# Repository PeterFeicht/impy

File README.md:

Bachelor's Thesis
=================

This project contains all of the stuff from my [bachelor's thesis](thesis.pdf).

The goal is to create an impedance spectrometer based on the
*Impedance Converter Network Analyzer* chip [AD5933][1] from Analog Devices.

The device uses an [STM32F4 Discovery board][2] by ST for interfacing with a PC
and MATLAB for controlling the measurement parameters.

[1]: http://www.analog.com/en/digital-to-analog-converters/direct-digital-synthesis-dds/ad5933/products/product.html
    "Analog Devices product page"
[2]: http://www.st.com/stm32f4-discovery "ST product page"
[3]: http://www.ti.com/tool/tmdssk3358 "TI product page"

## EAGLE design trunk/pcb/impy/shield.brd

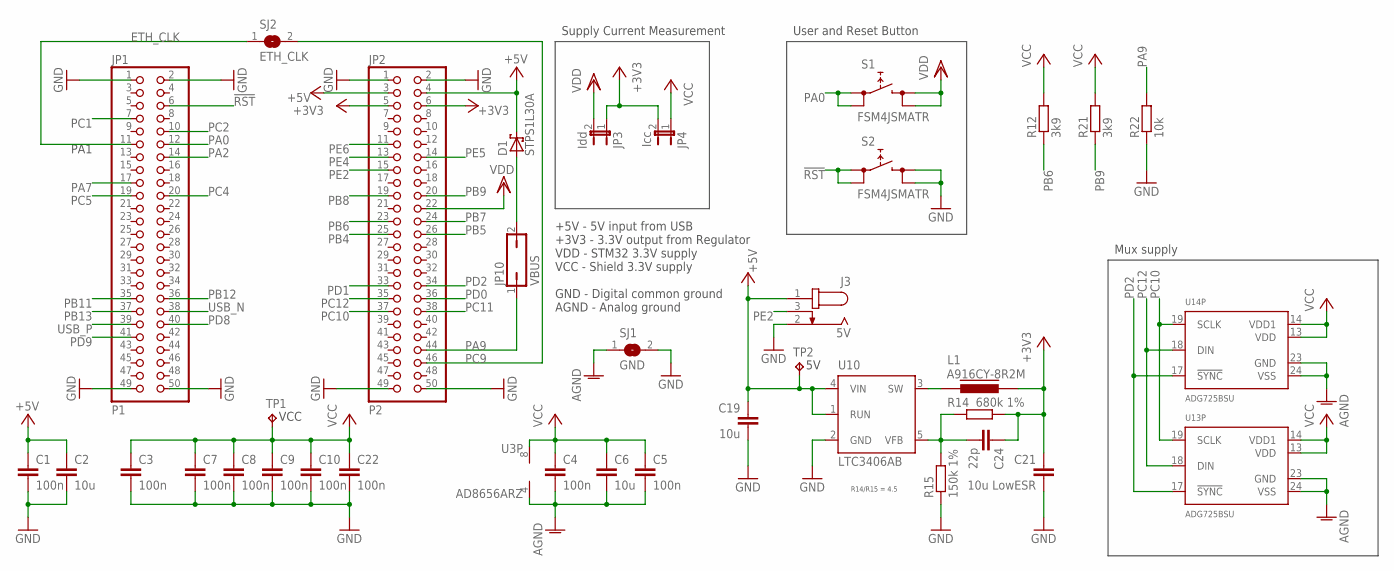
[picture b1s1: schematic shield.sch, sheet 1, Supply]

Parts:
C1, C3, C4, C5, C7, C8, C9, C10, C22: 100n; C0603
C2, C6: 10u; C0603
C19: 10u; C3216
C21: 10u LowESR; C3216
C24: 22p; C0603
D1: STPS1L30A; DO214AC
J3: 5V; JACK-SMD2.5
JP1: P1; 2X25-F
JP2: P2; 2X25-F
JP3: Idd; JP1
JP4: Icc; JP1
JP10: VBUS; JP1
L1: A916CY-8R2M; D63CB
R12, R21: 3k9; R0603
R14: 680k 1%; R0603
R15: 150k 1%; R0603
R22: 10k; R0603
S1, S2: FSM4JSMATR; FSM
SJ1: GND; SJ
SJ2: ETH_CLK; SJ
TP1, TP2: TPTP20R; TP20R
U3: AD8656ARZ; SOIC8
U10: LTC3406AB; TSOT23-5
U13, U14: ADG725BSU; TQFP48

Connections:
!RST: JP1.6, S2.1 (0), S2.2 (0)
+3V3: C21.1, C24.1, JP2.5, JP2.6, JP3.1, JP4.2, L1.2, R14.2
+5V: C1.1, C2.1, C19.1, D1.C, J3.1, JP2.3, JP2.4, TP2.TP, U10.1 (RUN), U10.4 (VIN); also elsewhere on the board
AGND: C4.2, C5.2, C6.2, SJ1.1, U3.4 (V-), U13.23 (GND), U13.24 (VSS), U14.23 (GND), U14.24 (VSS); also elsewhere on the board
ETH_CLK: JP1.11, SJ2.1; also elsewhere on the board
GND: C1.2, C2.2, C3.2, C7.2, C8.2, C9.2, C10.2, C19.2, C21.2, C22.2, J3.2 (3), JP1.1, JP1.2, JP1.49, JP1.50, JP2.1, JP2.2, JP2.49, JP2.50, R15.1, R22.1, S2.3 (1), S2.4 (1), SJ1.2, U10.2 (GND); also elsewhere on the board
unnamed: D1.A, JP10.2
unnamed: C24.2, R14.1, R15.2, U10.5 (VFB)
unnamed: L1.1, U10.3 (SW)
PA0: JP1.12, S1.1 (0), S1.2 (0)
PA2: JP1.14; also elsewhere on the board
PA7: JP1.17; also elsewhere on the board
PA9: JP2.44, JP10.1, R22.2
PB4: JP2.25; also elsewhere on the board
PB5: JP2.26; also elsewhere on the board
PB6: JP2.23, R12.1; also elsewhere on the board
PB7: JP2.24; also elsewhere on the board
PB8: JP2.19; also elsewhere on the board
PB9: JP2.20, R21.1; also elsewhere on the board
PB11: JP1.35; also elsewhere on the board
PB12: JP1.36; also elsewhere on the board
PB13: JP1.37; also elsewhere on the board
PC1: JP1.7; also elsewhere on the board
PC2: JP1.10; also elsewhere on the board
PC4: JP1.20; also elsewhere on the board
PC5: JP1.19; also elsewhere on the board
PC9: JP2.46, SJ2.2
PC10: JP2.37, U13.19 (SCLK), U14.19 (SCLK); also elsewhere on the board
PC11: JP2.38; also elsewhere on the board
PC12: JP2.35, U13.18 (DIN), U14.18 (DIN); also elsewhere on the board
PD0: JP2.36; also elsewhere on the board
PD1: JP2.33; also elsewhere on the board
PD2: JP2.34, U13.17 (!SYNC), U14.17 (!SYNC)
PD8: JP1.40; also elsewhere on the board
PD9: JP1.41; also elsewhere on the board
PE2: J3.3 (2), JP2.15
PE4: JP2.13; also elsewhere on the board
PE5: JP2.14; also elsewhere on the board
PE6: JP2.11; also elsewhere on the board
USB_N: JP1.38; also elsewhere on the board
USB_P: JP1.39; also elsewhere on the board
VCC: C3.1, C4.1, C5.1, C6.1, C7.1, C8.1, C9.1, C10.1, C22.1, JP4.1, R12.2, R21.2, TP1.TP, U3.8 (V+), U13.13 (VDD), U13.14 (VDD1), U14.13 (VDD), U14.14 (VDD1); also elsewhere on the board
VDD: JP2.22, JP3.2, S1.3 (1), S1.4 (1); also elsewhere on the board

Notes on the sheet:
+5V - 5V input from USB +3V3 - 3.3V output from Regulator VDD - STM32 3.3V supply VCC - Shield 3.3V supply GND - Digital common ground AGND - Analog ground
Supply Current Measurement
PA1
User and Reset Button
R14/R15 = 4.5
Mux supply

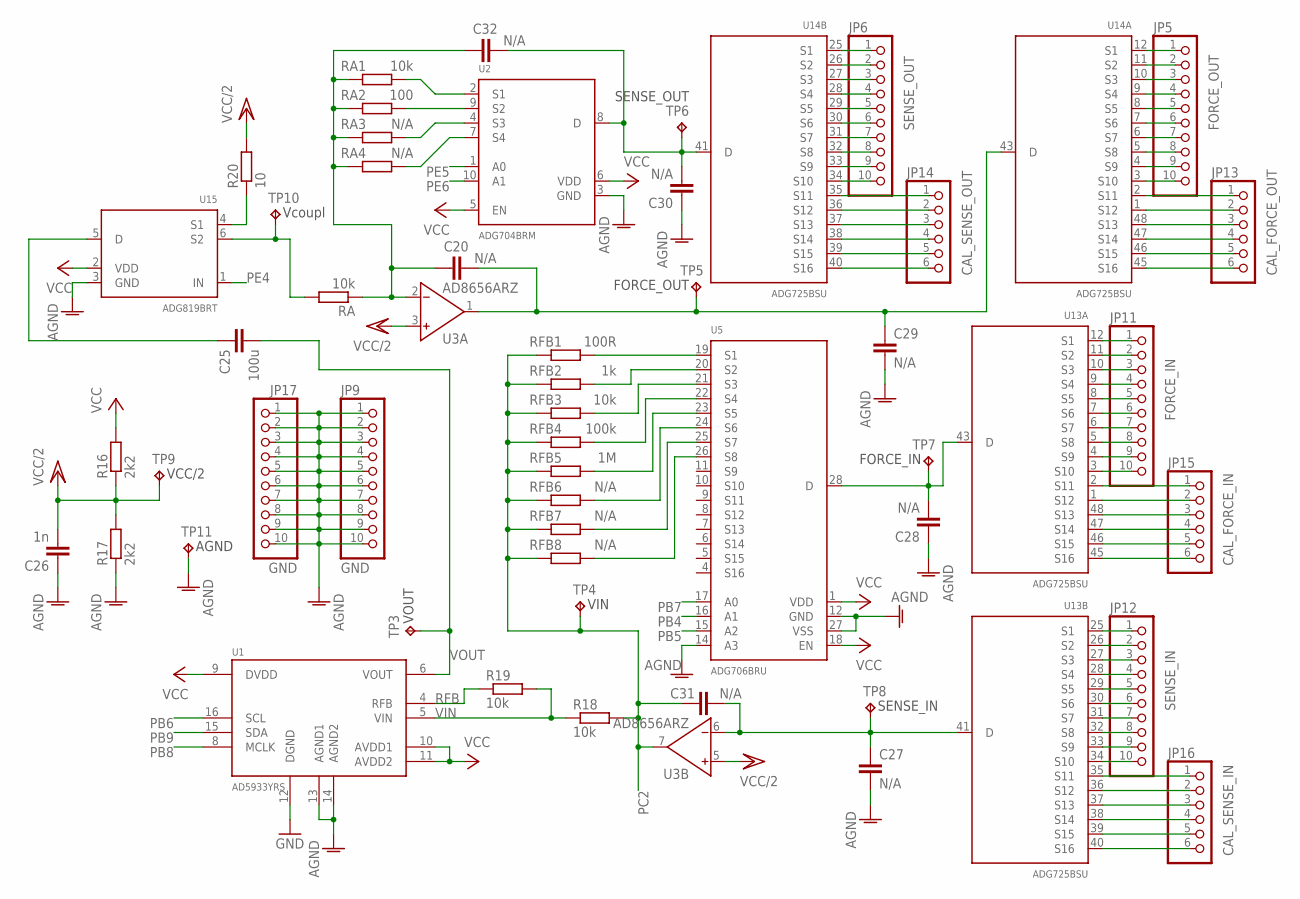
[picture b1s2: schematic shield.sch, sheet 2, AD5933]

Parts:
C20, C31, C32: N/A; C0603
C25: 100u; C1206
C26: 1n; C0603
C27, C28, C29, C30: N/A; C0805
JP5: FORCE_OUT; 1X10
JP6: SENSE_OUT; 1X10
JP9, JP17: GND; 1X10
JP11: FORCE_IN; 1X10
JP12: SENSE_IN; 1X10
JP13: CAL_FORCE_OUT; 1X06
JP14: CAL_SENSE_OUT; 1X06
JP15: CAL_FORCE_IN; 1X06
JP16: CAL_SENSE_IN; 1X06
R16, R17: 2k2; R0603
R18, R19: 10k; R0603
R20: 10; R0603
RA, RA1: 10k; R0603
RA2: 100; R0603
RA3, RA4: N/A; R0603
RFB1: 100R; R0603
RFB2: 1k; R0603
RFB3: 10k; R0603
RFB4: 100k; R0603
RFB5: 1M; R0603
RFB6, RFB7, RFB8: N/A; R0603
TP3, TP4, TP5, TP6, TP7, TP8, TP9, TP10: TPTP20R; TP20R
TP11: TPPAD1-13; P1-13
U1: AD5933YRS; SSOP16
U2: ADG704BRM; MSOP10
U3: AD8656ARZ; SOIC8
U5: ADG706BRU; TSSOP28
U13, U14: ADG725BSU; TQFP48
U15: ADG819BRT; SOT23-6

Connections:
AGND: C26.1, C27.2, C28.1, C29.2, C30.1, JP9.1, JP9.2, JP9.3, JP9.4, JP9.5, JP9.6, JP9.7, JP9.8, JP9.9, JP9.10, JP17.1, JP17.2, JP17.3, JP17.4, JP17.5, JP17.6, JP17.7, JP17.8, JP17.9, JP17.10, R17.1, TP11.TP, U1.13 (AGND1), U1.14 (AGND2), U2.3 (GND), U5.12 (GND), U5.14 (A3), U5.27 (VSS), U15.3 (GND); also elsewhere on the board
GND: U1.12 (DGND); also elsewhere on the board
unnamed 6: C31.1, R18.2, RFB1.2, RFB2.2, RFB3.2, RFB4.2, RFB5.2, RFB6.2, RFB7.2, RFB8.2, TP4.TP, U3.7 (OUT); also elsewhere on the board
unnamed: RA.2, TP10.TP, U15.6 (S2)
unnamed: C20.1, C32.1, RA.1, RA1.1, RA2.1, RA3.1, RA4.1, U3.2 (IN-)
unnamed: RA3.2, U2.4 (S3)
unnamed: RA4.2, U2.7 (S4)
unnamed: RFB1.1, U5.19 (S1)
unnamed: RFB2.1, U5.20 (S2)
unnamed: RFB3.1, U5.21 (S3)
unnamed: RFB4.1, U5.22 (S4)
unnamed: RFB5.1, U5.23 (S5)
unnamed: RFB6.1, U5.24 (S6)
unnamed: C27.1, C31.2, TP8.TP, U3.6 (IN-), U13.41 (D)
unnamed: C28.2, TP7.TP, U5.28 (D), U13.43 (D)
unnamed: C20.2, C29.1, TP5.TP, U3.1 (OUT), U14.43 (D)
unnamed: C30.2, C32.2, TP6.TP, U2.8 (D), U14.41 (D)
unnamed: JP12.1, U13.25 (S1)
unnamed: JP12.2, U13.26 (S2)
unnamed: JP12.3, U13.27 (S3)
unnamed: JP12.4, U13.28 (S4)
unnamed: JP12.5, U13.29 (S5)
unnamed: JP12.6, U13.30 (S6)
unnamed: JP12.7, U13.31 (S7)
unnamed: JP12.8, U13.32 (S8)
unnamed: JP12.9, U13.33 (S9)
unnamed: JP12.10, U13.34 (S10)
unnamed: JP11.1, U13.12 (S1)
unnamed: JP11.2, U13.11 (S2)
unnamed: JP11.3, U13.10 (S3)
unnamed: JP11.4, U13.9 (S4)
unnamed: JP11.5, U13.8 (S5)
unnamed: JP11.6, U13.7 (S6)
unnamed: JP11.7, U13.6 (S7)
unnamed: JP11.8, U13.5 (S8)
unnamed: JP11.9, U13.4 (S9)
unnamed: JP11.10, U13.3 (S10)
unnamed: JP5.1, U14.12 (S1)
unnamed: JP5.2, U14.11 (S2)
unnamed: JP5.3, U14.10 (S3)
unnamed: JP5.4, U14.9 (S4)
unnamed: JP5.5, U14.8 (S5)
unnamed: JP5.6, U14.7 (S6)
unnamed: JP5.7, U14.6 (S7)
unnamed: JP5.8, U14.5 (S8)
unnamed: JP5.9, U14.4 (S9)
unnamed: JP5.10, U14.3 (S10)
unnamed: JP6.1, U14.25 (S1)
unnamed: JP6.2, U14.26 (S2)
unnamed: JP6.3, U14.27 (S3)
unnamed: JP6.4, U14.28 (S4)
unnamed: JP6.5, U14.29 (S5)
unnamed: JP6.6, U14.30 (S6)
unnamed: JP6.7, U14.31 (S7)
unnamed: JP6.8, U14.32 (S8)
unnamed: JP6.9, U14.33 (S9)
unnamed: JP6.10, U14.34 (S10)
unnamed: JP13.1, U14.2 (S11)
unnamed: JP13.2, U14.1 (S12)
unnamed: JP13.3, U14.48 (S13)
unnamed: JP13.4, U14.47 (S14)
unnamed: JP13.5, U14.46 (S15)
unnamed: JP13.6, U14.45 (S16)
unnamed: JP14.1, U14.35 (S11)
unnamed: JP14.2, U14.36 (S12)
unnamed: JP14.3, U14.37 (S13)
unnamed: JP14.4, U14.38 (S14)
unnamed: JP14.5, U14.39 (S15)
unnamed: JP14.6, U14.40 (S16)
unnamed: JP15.1, U13.2 (S11)
unnamed: JP15.2, U13.1 (S12)
unnamed: JP15.3, U13.48 (S13)
unnamed: JP15.4, U13.47 (S14)
unnamed: JP15.5, U13.46 (S15)
unnamed: JP15.6, U13.45 (S16)
unnamed: JP16.1, U13.35 (S11)
unnamed: JP16.2, U13.36 (S12)
unnamed: JP16.3, U13.37 (S13)
unnamed: JP16.4, U13.38 (S14)
unnamed: JP16.5, U13.39 (S15)
unnamed: JP16.6, U13.40 (S16)
unnamed: RA2.2, U2.9 (S2)
unnamed: RA1.2, U2.2 (S1)
unnamed: RFB7.1, U5.25 (S7)
unnamed: RFB8.1, U5.26 (S8)
unnamed: C25.1, U15.5 (D)
unnamed: R20.1, U15.4 (S1)
PB4: U5.16 (A1); also elsewhere on the board
PB5: U5.15 (A2); also elsewhere on the board
PB6: U1.16 (SCL); also elsewhere on the board
PB7: U5.17 (A0); also elsewhere on the board
PB8: U1.8 (MCLK); also elsewhere on the board
PB9: U1.15 (SDA); also elsewhere on the board
PE4: U15.1 (IN); also elsewhere on the board
PE5: U2.1 (A0); also elsewhere on the board
PE6: U2.10 (A1); also elsewhere on the board
RFB: R19.1, U1.4 (RFB)
VCC: R16.2, U1.9 (DVDD), U1.10 (AVDD1), U1.11 (AVDD2), U2.5 (EN), U2.6 (VDD), U5.1 (VDD), U5.18 (EN), U15.2 (VDD); also elsewhere on the board
VCC/2: C26.2, R16.1, R17.2, R20.2, TP9.TP, U3.3 (IN+), U3.5 (IN+)
VIN: R18.1, R19.2, U1.5 (VIN)
VOUT: C25.2, TP3.TP, U1.6 (VOUT)

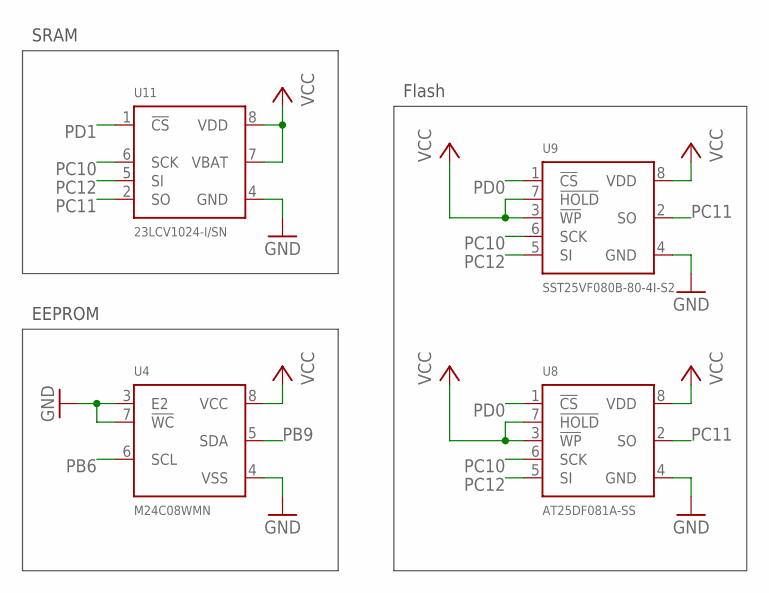
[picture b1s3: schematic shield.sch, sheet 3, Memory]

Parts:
U4: M24C08WMN; SO8
U8: AT25DF081A-SS; SO8
U9: SST25VF080B-80-4I-S2; SOIC8
U11: 23LCV1024-I/SN; SO8

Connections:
GND: U4.3 (E2), U4.4 (VSS), U4.7 (!WC), U8.4 (GND), U9.4 (GND), U11.4 (GND); also elsewhere on the board
PB6: U4.6 (SCL); also elsewhere on the board
PB9: U4.5 (SDA); also elsewhere on the board
PC10: U8.6 (SCK), U9.6 (SCK), U11.6 (SCK); also elsewhere on the board
PC11: U8.2 (SO), U9.2 (SO), U11.2 (SO); also elsewhere on the board
PC12: U8.5 (SI), U9.5 (SI), U11.5 (SI); also elsewhere on the board
PD0: U8.1 (!CS), U9.1 (!CS); also elsewhere on the board
PD1: U11.1 (!CS); also elsewhere on the board
VCC: U4.8 (VCC), U8.3 (!WP), U8.7 (!HOLD), U8.8 (VDD), U9.3 (!WP), U9.7 (!HOLD), U9.8 (VDD), U11.7 (VBAT), U11.8 (VDD); also elsewhere on the board

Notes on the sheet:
EEPROM
Flash
SRAM

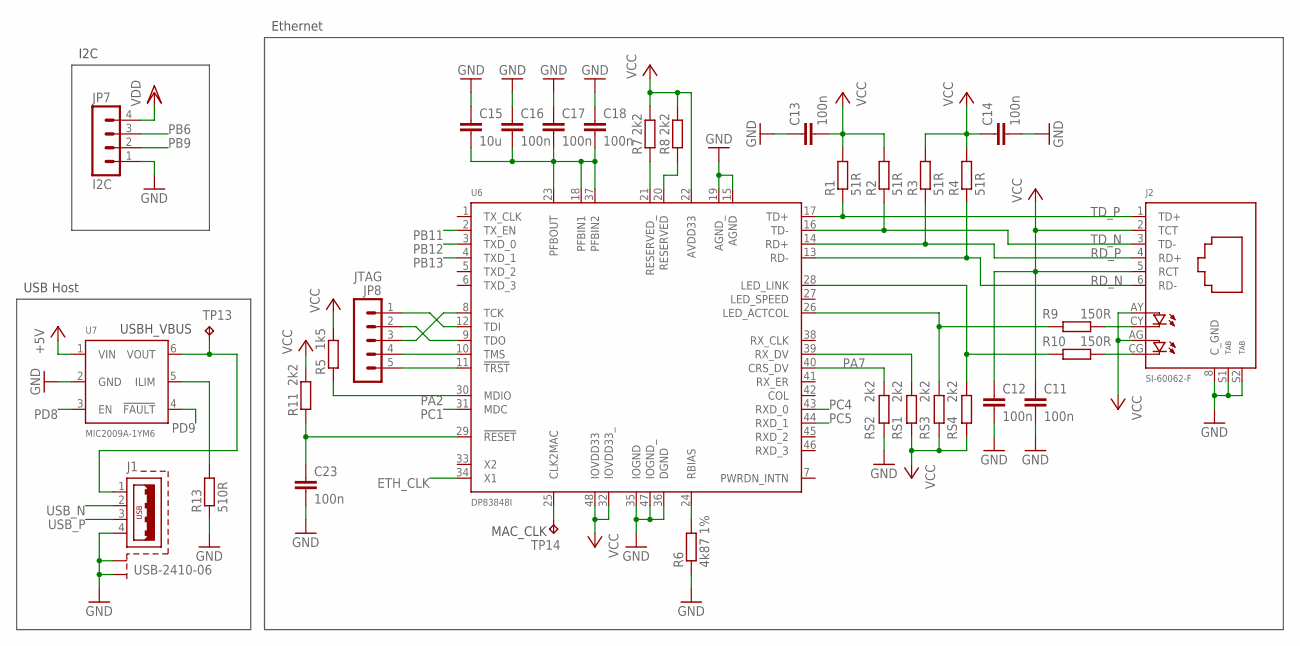
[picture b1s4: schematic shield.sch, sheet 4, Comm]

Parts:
C11, C12, C13, C14, C16, C17, C18, C23: 100n; C0603
C15: 10u; C0603
J1: USB-2410-06
J2: SI-60062-F
JP7: I2C; MA04-1
JP8: JTAG; MA05-1
R1, R2, R3, R4: 51R; R0603
R5: 1k5; R0603
R6: 4k87 1%; R0603
R7, R8, R11: 2k2; R0603
R9, R10: 150R; R0603
R13: 510R; R0603
RS1, RS2, RS3, RS4: 2k2; R0603
TP13, TP14: TPTP20R; TP20R
U6: DP83848I; LQFP48
U7: MIC2009A-1YM6; SOT23-6

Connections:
+5V: U7.1 (VIN); also elsewhere on the board
ETH_CLK: U6.34 (X1); also elsewhere on the board
GND: C11.2, C12.2, C13.1, C14.2, C15.1, C16.1, C17.1, C18.1, C23.2, J1.4 (GND), J1.S1, J1.S2, J2.8 (C_GND), J2.S1 (TAB1), J2.S2 (TAB2), JP7.1, R6.1, R13.1, RS2.2, U6.15 (AGND), U6.19 (AGND_), U6.35 (IOGND), U6.36 (DGND), U6.47 (IOGND_), U7.2 (GND); also elsewhere on the board
unnamed: J2.CY, R9.2
unnamed: RS1.2, U6.39 (RX_DV)
unnamed: R9.1, RS3.2, U6.26 (LED_ACTCOL)
unnamed: R10.1, RS4.2, U6.28 (LED_LINK)
unnamed: C15.2, C16.2, C17.2, C18.2, U6.18 (PFBIN1), U6.23 (PFBOUT), U6.37 (PFBIN2)
unnamed: J2.CG, R10.2
unnamed: J1.1 (VCC), TP13.TP, U7.6 (VOUT)
unnamed: JP8.1, U6.12 (TDI)
unnamed: JP8.2, U6.9 (TDO)
unnamed: JP8.3, U6.8 (TCK)
unnamed: JP8.4, U6.10 (TMS)
unnamed: JP8.5, U6.11 (!TRST)
unnamed: C23.1, R11.1, U6.29 (!RESET)
unnamed: R6.2, U6.24 (RBIAS)
unnamed: R8.1, U6.20 (RESERVED)
unnamed: R7.1, U6.21 (RESERVED_)
unnamed: R13.2, U7.5 (ILIM)
unnamed: TP14.TP, U6.25 (CLK2MAC)
PA2: R5.1, U6.30 (MDIO); also elsewhere on the board
PA7: RS2.1, U6.40 (CRS_DV); also elsewhere on the board
PB6: JP7.3; also elsewhere on the board
PB9: JP7.2; also elsewhere on the board
PB11: U6.2 (TX_EN); also elsewhere on the board
PB12: U6.3 (TXD_0); also elsewhere on the board
PB13: U6.4 (TXD_1); also elsewhere on the board
PC1: U6.31 (MDC); also elsewhere on the board
PC4: U6.43 (RXD_0); also elsewhere on the board
PC5: U6.44 (RXD_1); also elsewhere on the board
PD8: U7.3 (EN); also elsewhere on the board
PD9: U7.4 (!FAULT); also elsewhere on the board
RD_N: J2.6 (RD-), R4.1, U6.13 (RD-)
RD_P: J2.4 (RD+), R3.1, U6.14 (RD+)
TD_N: J2.3 (TD-), R2.1, U6.16 (TD-)
TD_P: J2.1 (TD+), R1.1, U6.17 (TD+)
USB_N: J1.2 (D-); also elsewhere on the board
USB_P: J1.3 (D+); also elsewhere on the board
VCC: C11.1, C12.1, C13.2, C14.1, J2.2 (TCT), J2.5 (RCT), J2.AG, J2.AY, R1.2, R2.2, R3.2, R4.2, R5.2, R7.2, R8.2, R11.2, RS1.1, RS3.1, RS4.1, U6.22 (AVDD33), U6.32 (IOVDD33_), U6.48 (IOVDD33); also elsewhere on the board
VDD: JP7.4; also elsewhere on the board

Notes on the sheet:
I2C
Ethernet
USB Host

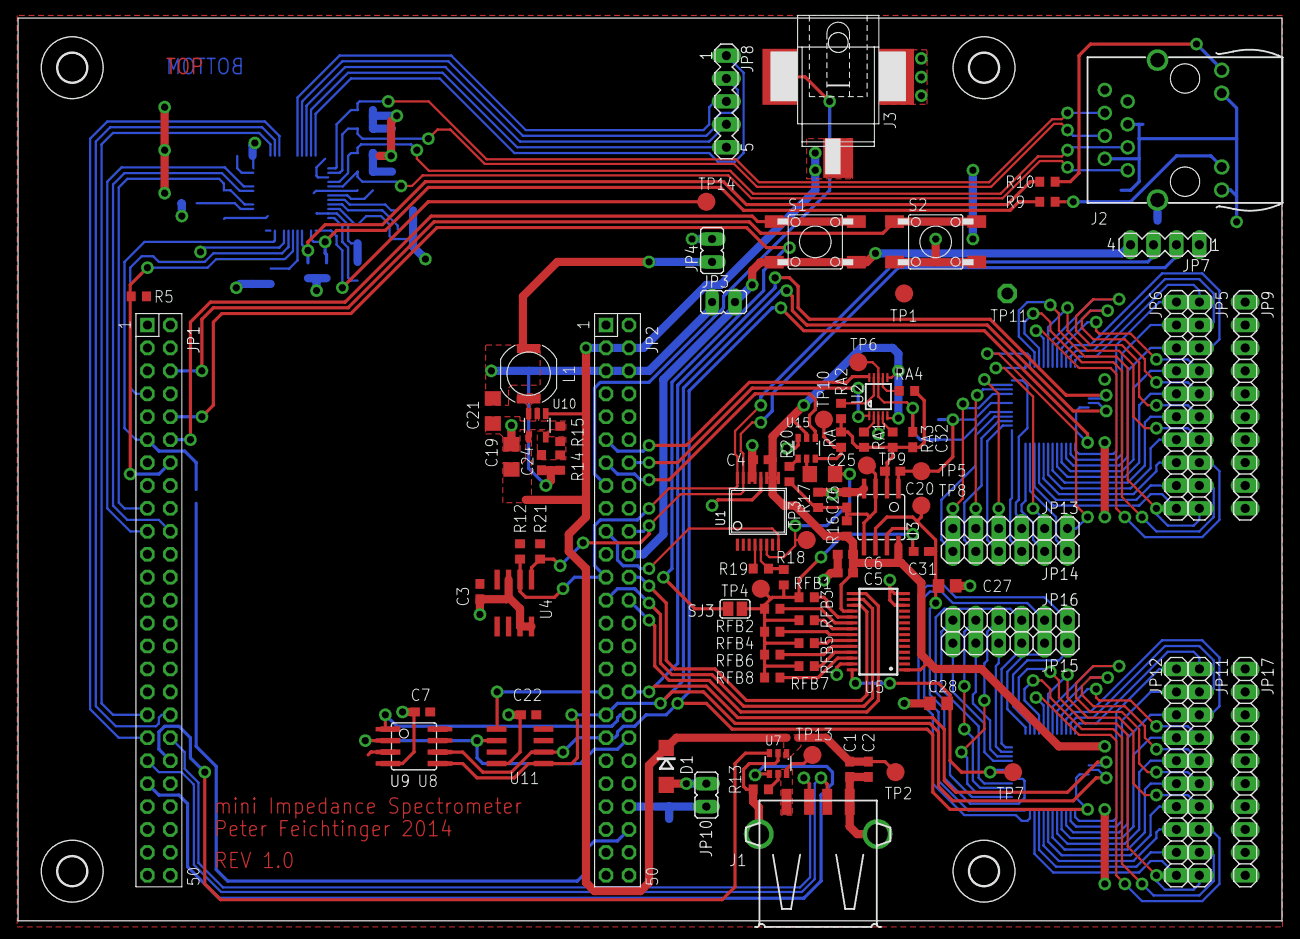
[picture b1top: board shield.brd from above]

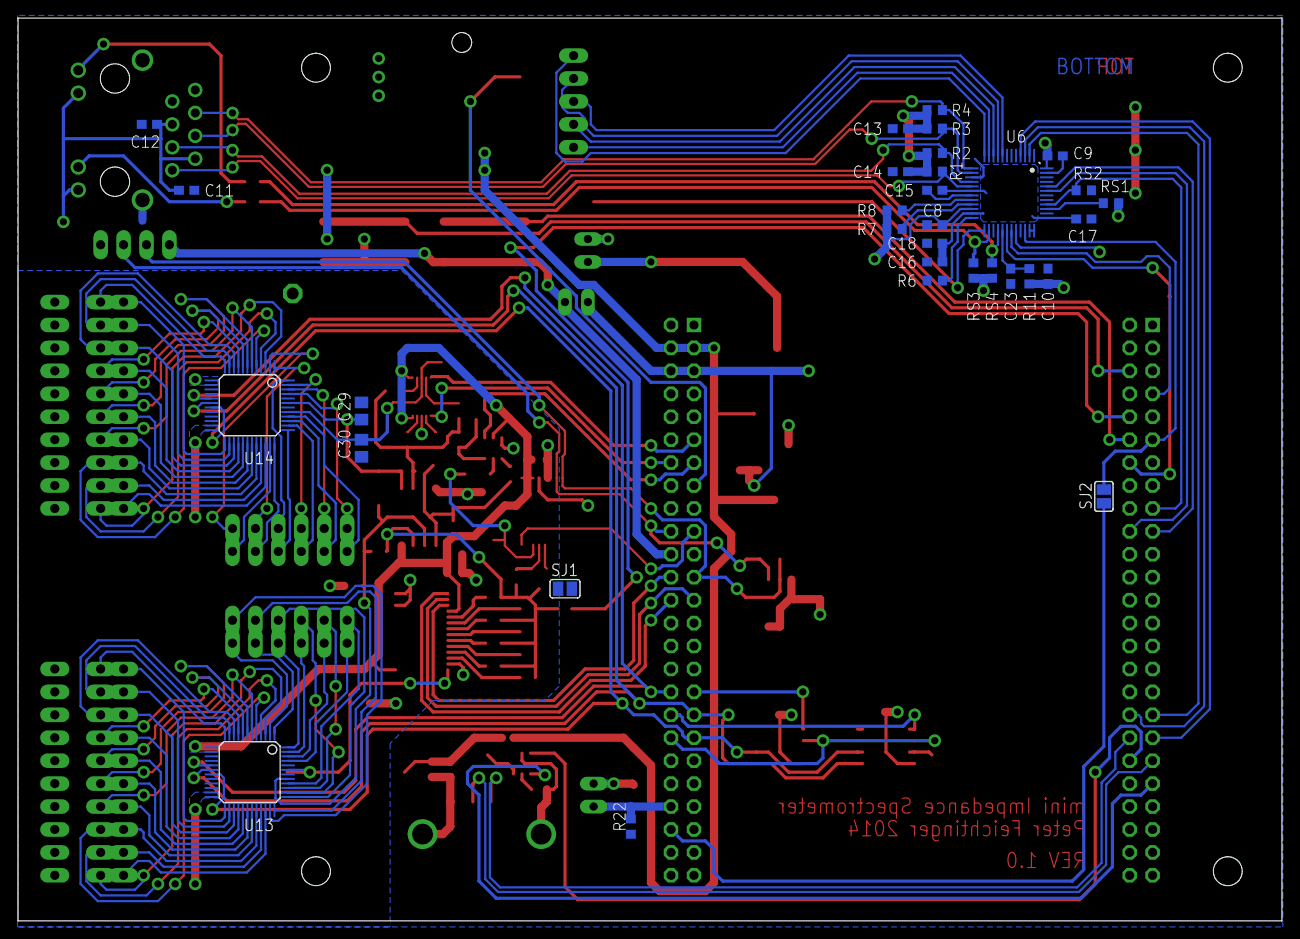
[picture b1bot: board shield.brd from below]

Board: 2 copper layers, 140.0 x 100.0 mm, 129 parts (32 on the bottom side), 154 nets.

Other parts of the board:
SJ3: OVFL; SJ
U$1, U$2, U$3, U$4: 3,2

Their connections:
unnamed 6: SJ3.2; also elsewhere on the board
PC2: SJ3.1; also elsewhere on the board

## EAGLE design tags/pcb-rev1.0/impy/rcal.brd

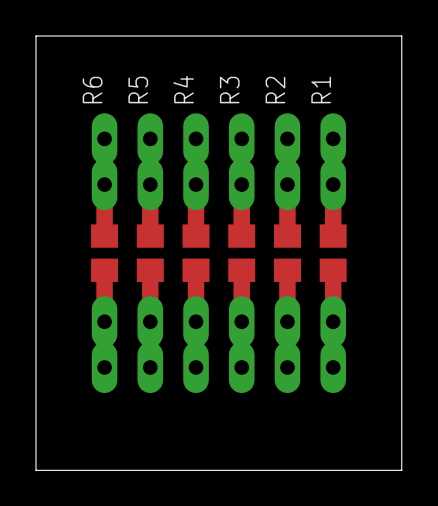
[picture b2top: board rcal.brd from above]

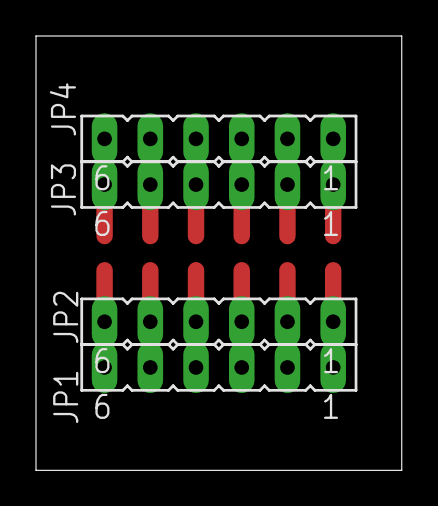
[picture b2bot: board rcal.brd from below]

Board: 2 copper layers, 20.3 x 24.1 mm, 10 parts (4 on the bottom side), 12 nets.

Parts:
JP1, JP2, JP3, JP4: FE06
R1: 10R; R0805
R2: 100R; R0805
R3: 1k; R0805
R4: 10k; R0805
R5: 100k; R0805
R6: 1M; R0805

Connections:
unnamed: JP1.6, JP2.6, R1.1
unnamed: JP1.5, JP2.5, R2.1
unnamed: JP1.4, JP2.4, R3.1
unnamed: JP1.3, JP2.3, R4.1
unnamed: JP1.2, JP2.2, R5.1
unnamed: JP1.1, JP2.1, R6.1
unnamed: JP3.6, JP4.6, R1.2
unnamed: JP3.5, JP4.5, R2.2
unnamed: JP3.4, JP4.4, R3.2
unnamed: JP3.3, JP4.3, R4.2
unnamed: JP3.2, JP4.2, R5.2
unnamed: JP3.1, JP4.1, R6.2

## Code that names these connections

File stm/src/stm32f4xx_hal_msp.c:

/**
 * @file    stm32f4xx_hal_msp.c
 * @author  Peter Feichtinger
 * @date    14.04.2014
 * @brief   Provides MSP initialization code.
 */

// Includes -------------------------------------------------------------------
#include "stm32f4xx_hal.h"

// Exported functions ---------------------------------------------------------

/**
 * Initializes the I2C MSP.
 * 
 * @param hi2c I2C handle
 */
void HAL_I2C_MspInit(I2C_HandleTypeDef* hi2c) {
    GPIO_InitTypeDef GPIO_InitStruct;
    if(hi2c->Instance == I2C1) {
        __I2C1_CLK_ENABLE();
        
        /*
         * GPIO configuration:
         *  PB6: I2C1_SCL
         *  PB9: I2C1_SDA
         */
        GPIO_InitStruct.Pin = GPIO_PIN_6 | GPIO_PIN_9;
        GPIO_InitStruct.Mode = GPIO_MODE_AF_OD;
        GPIO_InitStruct.Pull = GPIO_NOPULL;
        GPIO_InitStruct.Speed = GPIO_SPEED_LOW;
        GPIO_InitStruct.Alternate = GPIO_AF4_I2C1;
        HAL_GPIO_Init(GPIOB, &GPIO_InitStruct);
        
        // Set I2C interrupt to the lowest priority
        HAL_NVIC_SetPriority(I2C1_EV_IRQn, 10, 0);
        NVIC_EnableIRQ(I2C1_EV_IRQn);
    }
}

/**
 * De-initializes the I2C MSP.
 * 
 * @param hi2c I2C handle
 */
void HAL_I2C_MspDeInit(I2C_HandleTypeDef* hi2c) {
    if(hi2c->Instance == I2C1) {
        __I2C1_CLK_DISABLE();
        HAL_GPIO_DeInit(GPIOB, GPIO_PIN_6 | GPIO_PIN_9);
        NVIC_DisableIRQ(I2C1_EV_IRQn);
    }
}

/**
 * Initializes the SPI MSP.
 * 
 * @param hspi SPI handle
 */
void HAL_SPI_MspInit(SPI_HandleTypeDef* hspi) {
    GPIO_InitTypeDef GPIO_InitStruct;
    if(hspi->Instance == SPI3) {
        __SPI3_CLK_ENABLE();
        
        /*
         * GPIO configuration:
         *  PC10: SPI3_SCK
         *  PC11: SPI3_MISO
         *  PC12: SPI3_MOSI
         */
        GPIO_InitStruct.Pin = GPIO_PIN_10 | GPIO_PIN_11 | GPIO_PIN_12;
        GPIO_InitStruct.Mode = GPIO_MODE_AF_PP;
        GPIO_InitStruct.Pull = GPIO_NOPULL;
        GPIO_InitStruct.Speed = GPIO_SPEED_HIGH;
        GPIO_InitStruct.Alternate = GPIO_AF6_SPI3;
        HAL_GPIO_Init(GPIOC, &GPIO_InitStruct);
        
        // Set SPI interrupt to the lowest priority
        HAL_NVIC_SetPriority(SPI3_IRQn, 10, 0);
        NVIC_EnableIRQ(SPI3_IRQn);
    }
}

/**
 * De-initializes the SPI MSP.
 * 
 * @param hspi SPI handle
 */
void HAL_SPI_MspDeInit(SPI_HandleTypeDef* hspi) {
    if(hspi->Instance == SPI3) {
        __SPI3_CLK_DISABLE();
        HAL_GPIO_DeInit(GPIOD, GPIO_PIN_0 | GPIO_PIN_1 | GPIO_PIN_2);
        HAL_GPIO_DeInit(GPIOC, GPIO_PIN_10 | GPIO_PIN_11 | GPIO_PIN_12);
        NVIC_DisableIRQ(SPI3_IRQn);
    }
}

/**
 * Initializes the TIM MSP.
 * 
 * @param htim TIM handle
 */
void HAL_TIM_Base_MspInit(TIM_HandleTypeDef* htim) {
    GPIO_InitTypeDef GPIO_InitStruct;
    if(htim->Instance == TIM3) {
        __TIM3_CLK_ENABLE();
        HAL_NVIC_SetPriority(TIM3_IRQn, 7, 0);
        NVIC_EnableIRQ(TIM3_IRQn);
        
    } else if(htim->Instance == TIM10) {
        __TIM10_CLK_ENABLE();
        
        /*
         * GPIO configuration:
         *  PB8: TIM10_CH1
         */
        GPIO_InitStruct.Pin = GPIO_PIN_8;
        GPIO_InitStruct.Mode = GPIO_MODE_AF_PP;
        GPIO_InitStruct.Pull = GPIO_NOPULL;
        GPIO_InitStruct.Speed = GPIO_SPEED_FAST;
        GPIO_InitStruct.Alternate = GPIO_AF3_TIM10;
        HAL_GPIO_Init(GPIOB, &GPIO_InitStruct);
    }
}

/**
 * De-initializes the TIM MSP.
 * 
 * @param htim TIM handle
 */
void HAL_TIM_Base_MspDeInit(TIM_HandleTypeDef* htim) {
    if(htim->Instance == TIM3) {
        __TIM3_CLK_DISABLE();
        NVIC_DisableIRQ(TIM3_IRQn);
        
    } else if(htim->Instance == TIM10) {
        __TIM10_CLK_DISABLE();
        HAL_GPIO_DeInit(GPIOB, GPIO_PIN_8);
    }
}

// ----------------------------------------------------------------------------

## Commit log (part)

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2014-06-24 * stm/impy: (main.c) Change default values for start frequency, feedback resistor and autorange. (command-line.txt) Update documentation for changed values.
2014-06-24 * stm/impy: (ad5933.h) Add constant for lowest sweep frequencies with the respective clock sources. Change order of constant declarations to be sorted from high to low.
2014-06-24 * stm/impy: (ad5933.h) Remove constant for timer handle and add argument to AD5933_Init function instead. (ad5933.c) Add timer handle variable and argument to AD5933_Init function. (main.c) Add timer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
2014-06-24 * stm/impy: (ad5933.c) Implement clock source change during a sweep.
    The phase error when using a different clock source than was calibrated with is considerable, maybe we need to do a phase calibration in each frequency range. Therefore the gain factor structures wou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
    The alternative would be to let the user manage multiple gain factors for different frequency ranges.
2014-06-27 * stm/impy: (stm32f4xx_it.c) Change hard fault handler to flash the red LED.
2014-06-28 * stm/impy: (main.c) Update Board_Calibrate to new AD5933 driver calibration interface. (convert.c) Update Convert_ConvertGainFactor to handle new gain factor format.
2014-06-29 * stm/impy: (usbd_vcp_if.c) Don't call console with empty command.
2014-06-29 * stm/impy: (ad5933.c) Remove unnecessary private function AD5933_NeedClockChange, only one line that's used in one place.
2014-06-29 * matlab: Add script to test impy_getall function.
2014-06-29 * matlab: (readdata.m, readdata_p.m) Add proper documentation to functions.
2014-06-29 * matlab: Add script to test the whole measurement process, including functions impy_setsweep, impy_calibrate, impy_start, impy_poll and impy_read (both polar and raw format), with option to compare 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
2014-06-30 * matlab: (impy_setsweep.m) Add documentation for required and optional fields.
2014-06-30 * stm/impy: (console.c) Remove debug commands char-from-flag, read and ad-i2c because they are no longer needed.
2014-06-30 * stm/impy: (console.h, console.c) Change signature of Console_ProcessLine to take a Console_Interface pointer. (console.c) Add variable for the interface.
2014-06-30 * stm/impy: (console.c) Replace all calls to VCP functions with calls to interface pointers. As a side note, this adds 840 bytes to the code size.
2014-06-30 * stm/impy: (ad5933.c, console.c, convert.c, main.c, usbd_vcp_if.c) Replace some parameter checks by assert or assert_param macro.
2014-07-04 * stm/impy: (ad5933.c) Improve documentation and add some structure comments.
2014-07-05 * stm/impy: Update STM32CubeF4 HAL and USB drivers to version 1.3.0.
2014-07-05 * stm/impy: (eeprom.h, eeprom.c) Rename functions with shorter module prefix.
2014-07-05 * stm/impy: (console.c) Add debug command output to output a single frequency on a specified port.
2014-07-05 * pcb/impy: (ime.dru) Change distance copper/dimension to 80mil.
2014-07-05 * stm/impy: (eeprom.h) Add structure definitions for configuration and settings buffers, add constants for memory organization and change access methods to read and write the new structures instead o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
2014-07-05 * stm/impy: (eeprom.h) Add macro to build I2C device address. Improve documentation. Add constant for EEPROM size.
2014-07-05 * stm/impy: Add CRC HAL driver file to build. (stm32f4xx_hal_conf.h) Enable HAL CRC module. (main.h, main.c) Add CRC handle variable. (mx_init.c) Add CRC initialization.
2014-07-05 * stm/impy: (eeprom.h) Change EE_TimerCallback to return current driver status.
2014-07-06 * stm/impy: (eeprom.h) Add status definitions for different writes.
2014-07-06 * stm/impy: (eeprom.h) Add constant for the EEPROM page size.
2014-07-06 * stm/impy: (eeprom.c) Fix bad buffer size in CRC calculation.
2014-07-06 * stm/impy: (eeprom.c) Add status assertion to exported functions.
2014-07-06 * stm/impy/system: (usbd_def.h) Avoid warning by conditionally defining HIBYTE and LOBYTE macros.
2014-07-06 * stm/impy: (eeprom.h) Avoid warning by conditionally defining HIBYTE and LOBYTE macros.
2014-07-06 * stm/impy: (mx_init.h, mx_init.c) Add function MX_Init_Ethernet to initialize Ethernet specific things, at the moment only the PLLI2S and MCO2 are configured. (mx_init.c) Remove conditional GPIO ana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
2014-07-06 * stm/impy: (console.c) Add parameter checks and unused attributes to some Ethernet and USB processing functions.
2014-07-06 * stm/impy: (main.h, main.c, console.c) Remove constant PORT_MIN, the first port is always 0.
2014-07-06 * stm/impy: (eeprom.h) Add fields for external memory sizes to EEPROM_ConfigurationBuffer. (main.c) Add default values to configuration structure initialization.
2014-07-06 * stm/impy: (eeprom.h, eeprom.c) Add driver prefix to function EE_GetStatus.
2014-07-06 * stm/impy: (main.h) Add constant for the state of the EEPROM E2 pin.
2014-07-06 * stm/impy: (eeprom.c) Fix data type for 16 bit addition.
2014-07-06 * stm/impy: (ad5933.h, mx_init.c) Update documentation.
2014-07-06 * stm/impy: (eeprom.h, eeprom.c) Make EE_IsBusy public.
2014-07-06 * stm/impy: (main.h) Add constant for EEPROM write interval and prototype for MarkSettingsDirty. (main.c) Implement writing settings to EEPROM, works beautifully.
2014-07-06 * stm/impy: (main.h, main.c) Add function WriteConfiguration to initiate a configuration write. (main.c) Add Ethernet initialization (just the call).
2014-07-07 * stm/impy: (mx_init.c) Fix missing CRC peripheral clock enable.
2014-07-07 * stm/impy: (ad5933.h) Change NUMEL macro.
2014-07-07 * stm/impy: (console.h) Add Console_CalibrateCallback function. (console.c) Add missing documentation. Change 'board calibrate' command to use callback instead of waiting. (main.c) Change calibration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
2014-07-09 * latex/presentations: Add second presentation with pictures. Add pr2.pdf to ignore list.
2014-07-10 * stm/impy: (console.c) Add debug command dump to dump EEPROM contents to console.
2014-07-11 * stm/impy: (util.h, util.c) Add functions MacAddressFromString and StringFromMacAddress to convert MAC addresses. (util.c) Add private function Util_ConvertHexDigit.
2014-07-11 * stm/impy: (console.c) Implement setup command. (string_en.h) Add strings for setup command.
2014-07-11 * stm/impy: (console.c) Add Ethernet, SRAM and flash memory info to 'board info' command.
2014-07-11 * stm/impy: (command-line.txt) Add possible MAC address format to setup help topic.
2014-07-11 * stm/impy: (main.c) Replace GCC pragmas with attributes for main function.
2014-07-11 * stm/impy: (util.c) Add parameter checks to MacAddressFromString and StringFromMacAddress.
2014-07-11 * stm/impy: (usbd_vcp_if.c) Remove unnecessary TODO tag.
2014-07-11 * stm/impy: (eeprom.c) Change EE_Init to check for EEPROM response and return success or error depending on the result, useful for dynamically determining if an EEPROM is fitted.
2014-07-11 * stm/impy: (main.h) Remove constant for EEPROM population and add extern variable declaration board_has_eeprom. (console.c) Use variable board_has_eeprom instead of constant.
2014-07-11 * stm/impy: (main.c) Replace duplicate code by call to MarkSettingsDirty in InitFromEEPROM.
2014-07-11 * stm/impy: (command-line.txt) Fix typo.
2014-07-11 * stm/impy: Add binary and documentation directories to ignore list. Add Doxyfile.
2014-07-11 * stm/impy: (usbd_vcp.c) Fix incomplete transfer when the size is a multiple of the packet size. This resolves issue 31.
2014-07-12 * stm/impy: (console.c) Remove debug command tim.
2014-07-12 * stm/impy: (ad5933.h, main.c) Minor comment changes.
2014-07-14 * stm/impy: (command-line.txt) Change range selection procedure, the highest current should be no more than 10mA to guarantee 3V output voltage swing. Add 'usb delete' command.
2014-07-15 * pcb/impy: (shield.sch) Add various compensation capacitors to the op amps.
2014-07-15 * pcb/impy: (shield.sch, shield.brd) Add solder jumper for overflow detect signal.
2014-07-15 * pcb/impy: (eagle.epf) Update EAGLE preference file.
2014-07-16 * latex/thesis: (dank.tex) Write acknowledgment, maybe I'll add some more people to thank.
2014-10-22 * latex/thesis: (thesis.tex) Change the document structure.
2014-10-22 * latex/thesis: (header.tex) Add file defs.tex for custom command definitions and move stuff from header.tex there.
2014-10-22 * latex/thesis: (thesis.tex) Include defs file.
2014-10-22 * stm/impy: Format the source code with a new style, opening braces are mostly on the same line now.
2014-10-22 * latex/thesis: (software.tex) Write Software chapter, mostly finished.
2014-10-24 * latex/thesis: (api.tex) Write API chapter, mostly finished.
2014-10-24 * stm/impy: (command-line.txt) Improve usage text.
2014-12-02 * latex/thesis: (software.tex, api.tex) Change wording and a section title.
2014-12-02 * latex/thesis: (hardware.tex) Start hardware chapter (introduction finished, analog front end started). * Add images: STM32F4 Discovery board, AD5933 block diagram and AFE block diagram.
2014-12-03 * latex/thesis: (hardware.tex) Add subsection for the AD5933 measurement procedure.
2014-12-03 * latex/thesis: (hardware.tex) Finish AFE subsection.
2014-12-03 * latex/thesis: (hardware.tex) Add section for power supply and memory.
2014-12-06 * latex/thesis: (hardware.tex) Change wording and rename figure schem_afe to afe_block.
2014-12-06 * latex/thesis: Add file gloss.txt to collect possible glossary entries.
2014-12-07 * latex/thesis: (manual.tex) Add overview section and description of most connectors.
2014-12-07 * latex/thesis: (manual.tex) Fix inconsistent connection overview label spacing.
2014-12-07 * latex/thesis: (defs.tex) Add command for typesetting console commands.
2014-12-07 * latex/thesis: (manual.tex) Complete subsection for first steps and add section for making measurements.
2014-12-08 * latex/thesis: (manual.tex) Add and complete subsection for the sweep configuration. * latex/thesis: (hardware.tex) Add label for the AD5933 measurement procedure subsection.
2014-12-08 * latex/thesis: (structure/header.tex) Add array package. * latex/thesis: (manual.tex) Add and complete subsections for starting a sweep and reading results.
2014-12-08 * latex/thesis: (manual.tex) Add and complete section for additional commands.
2014-12-09 * latex/thesis: Change draft versions of images pcb_frontback and device_connections to final and add Photoshop files.
2014-12-11 * matlab: (impy_read.m) Fix dead code.
2014-12-12 * latex/thesis: (header.tex) Add MATLAB interface function names as emphasized identifiers to listings.
2014-12-12 * latex/thesis: Add code directory with MATLAB demo script.
2014-12-15 * latex/presentations: Add final presentation with pictures. Add pr3.pdf to ignore list.
2014-12-17 * latex/thesis: (results.tex) Finish chapter about measurement results. * Add images of measurement results with 49R9, 5k6, 10k and 1M resistors and two LC circuits.
2014-12-17 * latex/thesis/bilder: Add script to crop PDF pages.
2014-12-17 * latex/thesis: (manual.tex) Add LED position to function description.
2014-12-17 * latex/thesis: (structure/header.tex) Remove unnecessary packages and add package for the Euro symbol. * latex/thesis: (structure/defs.tex): Remove unused command definitions.
2014-12-17 * latex/thesis: (structure/abstract.tex) Move English and German abstracts to the same page.
2014-12-19 * latex/thesis: (structure/coversheet.tex) Change date.
2014-12-26 Implement suggestions from Stefan Clara: * latex/thesis: (hardware.tex) Add reference for STM32F4 Discovery board image, add comment why the internal AD5933 clock source is used and elaborate on four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
2014-12-26 * latex/thesis: (software.tex) Add explanation of calibration types to AD5933 driver section.
2015-01-21 * Create tag for preliminary version of the thesis.
2015-05-30 * stm/impy: (_startup.c) Fix a typo in startup guard checks.
2018-10-14 Add .gitignore
